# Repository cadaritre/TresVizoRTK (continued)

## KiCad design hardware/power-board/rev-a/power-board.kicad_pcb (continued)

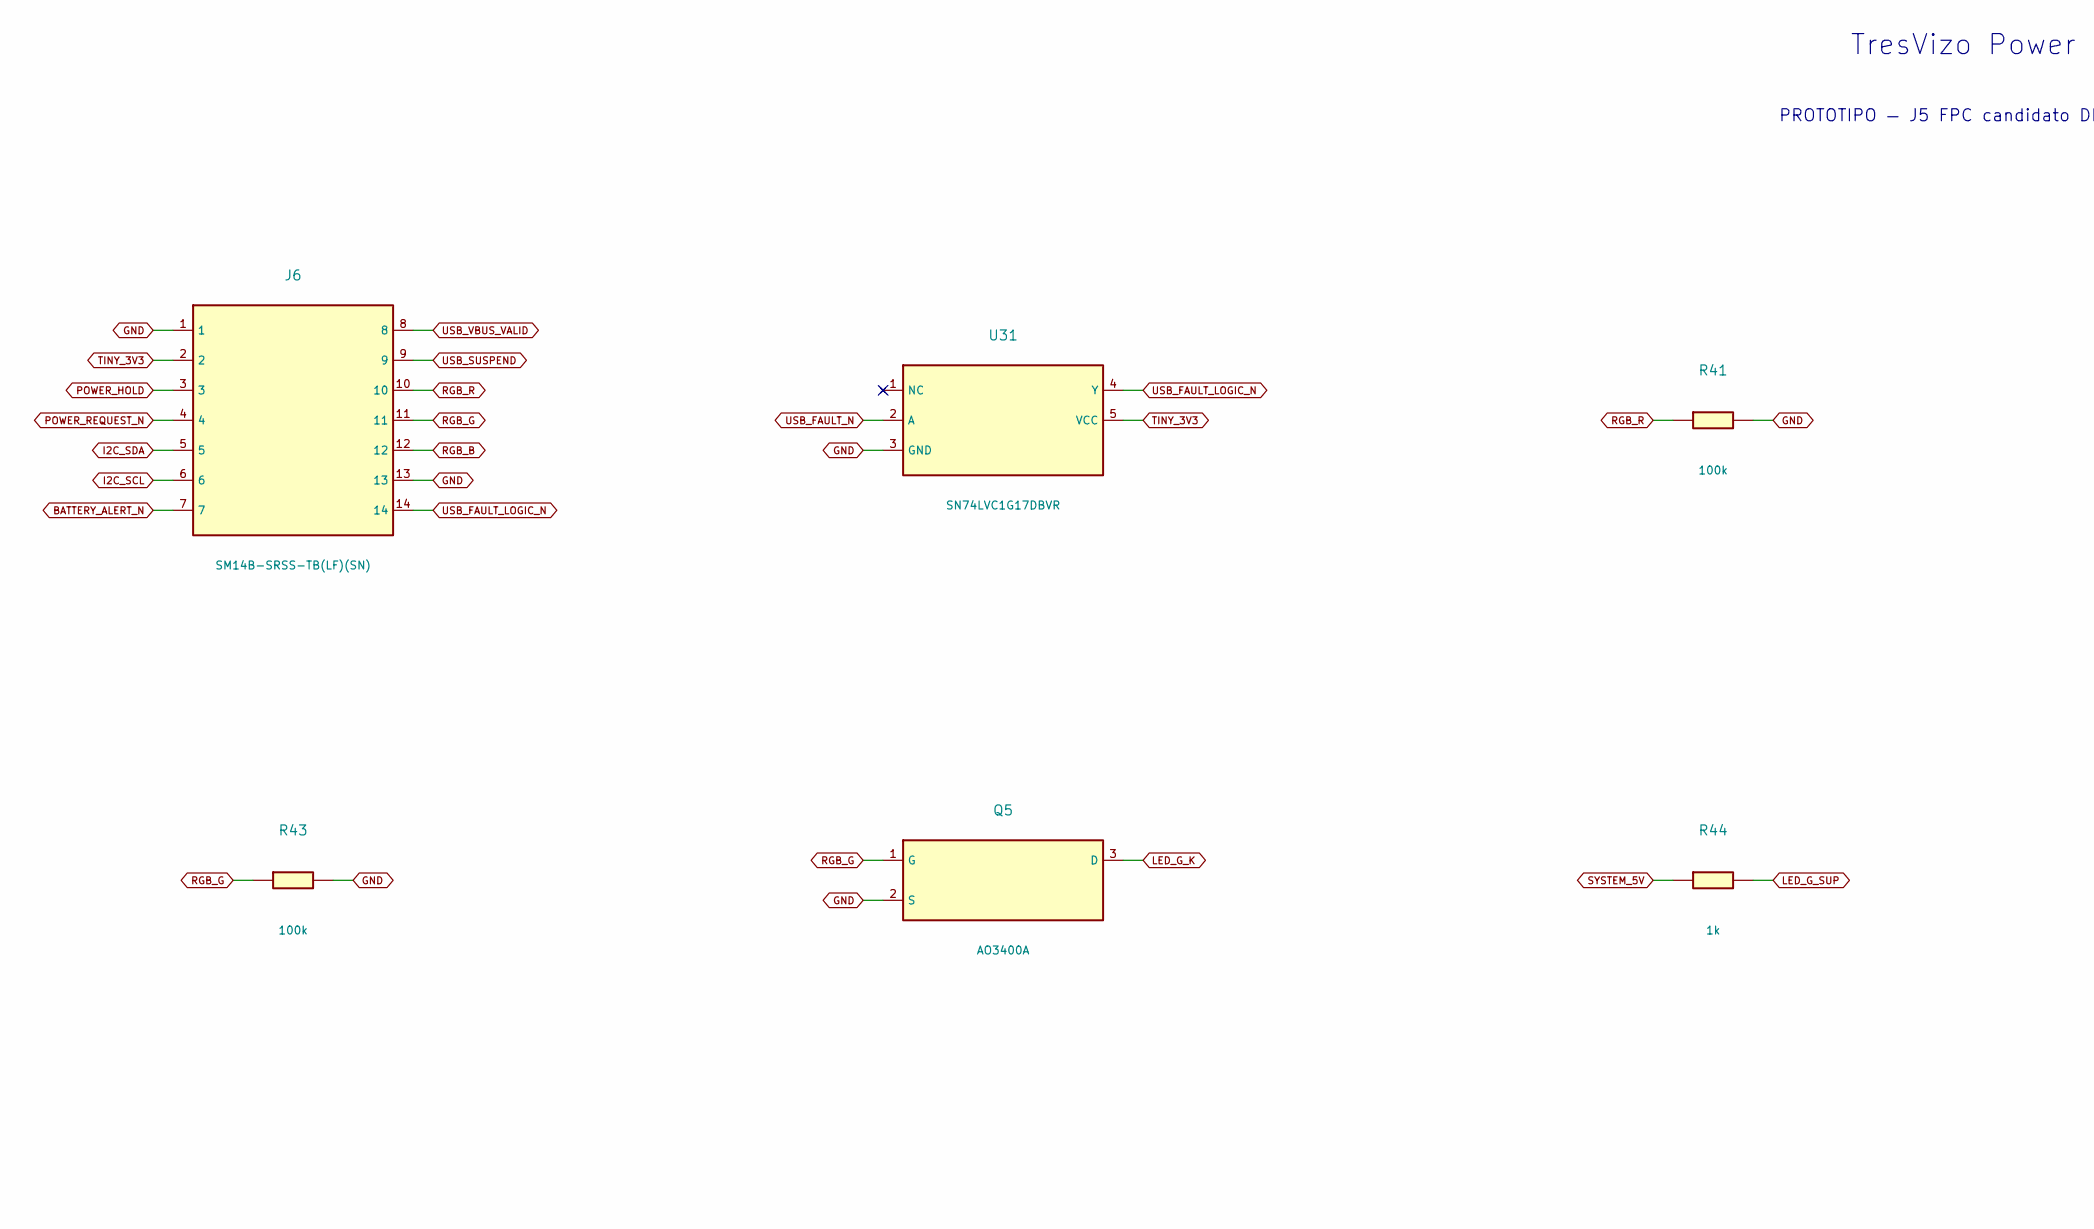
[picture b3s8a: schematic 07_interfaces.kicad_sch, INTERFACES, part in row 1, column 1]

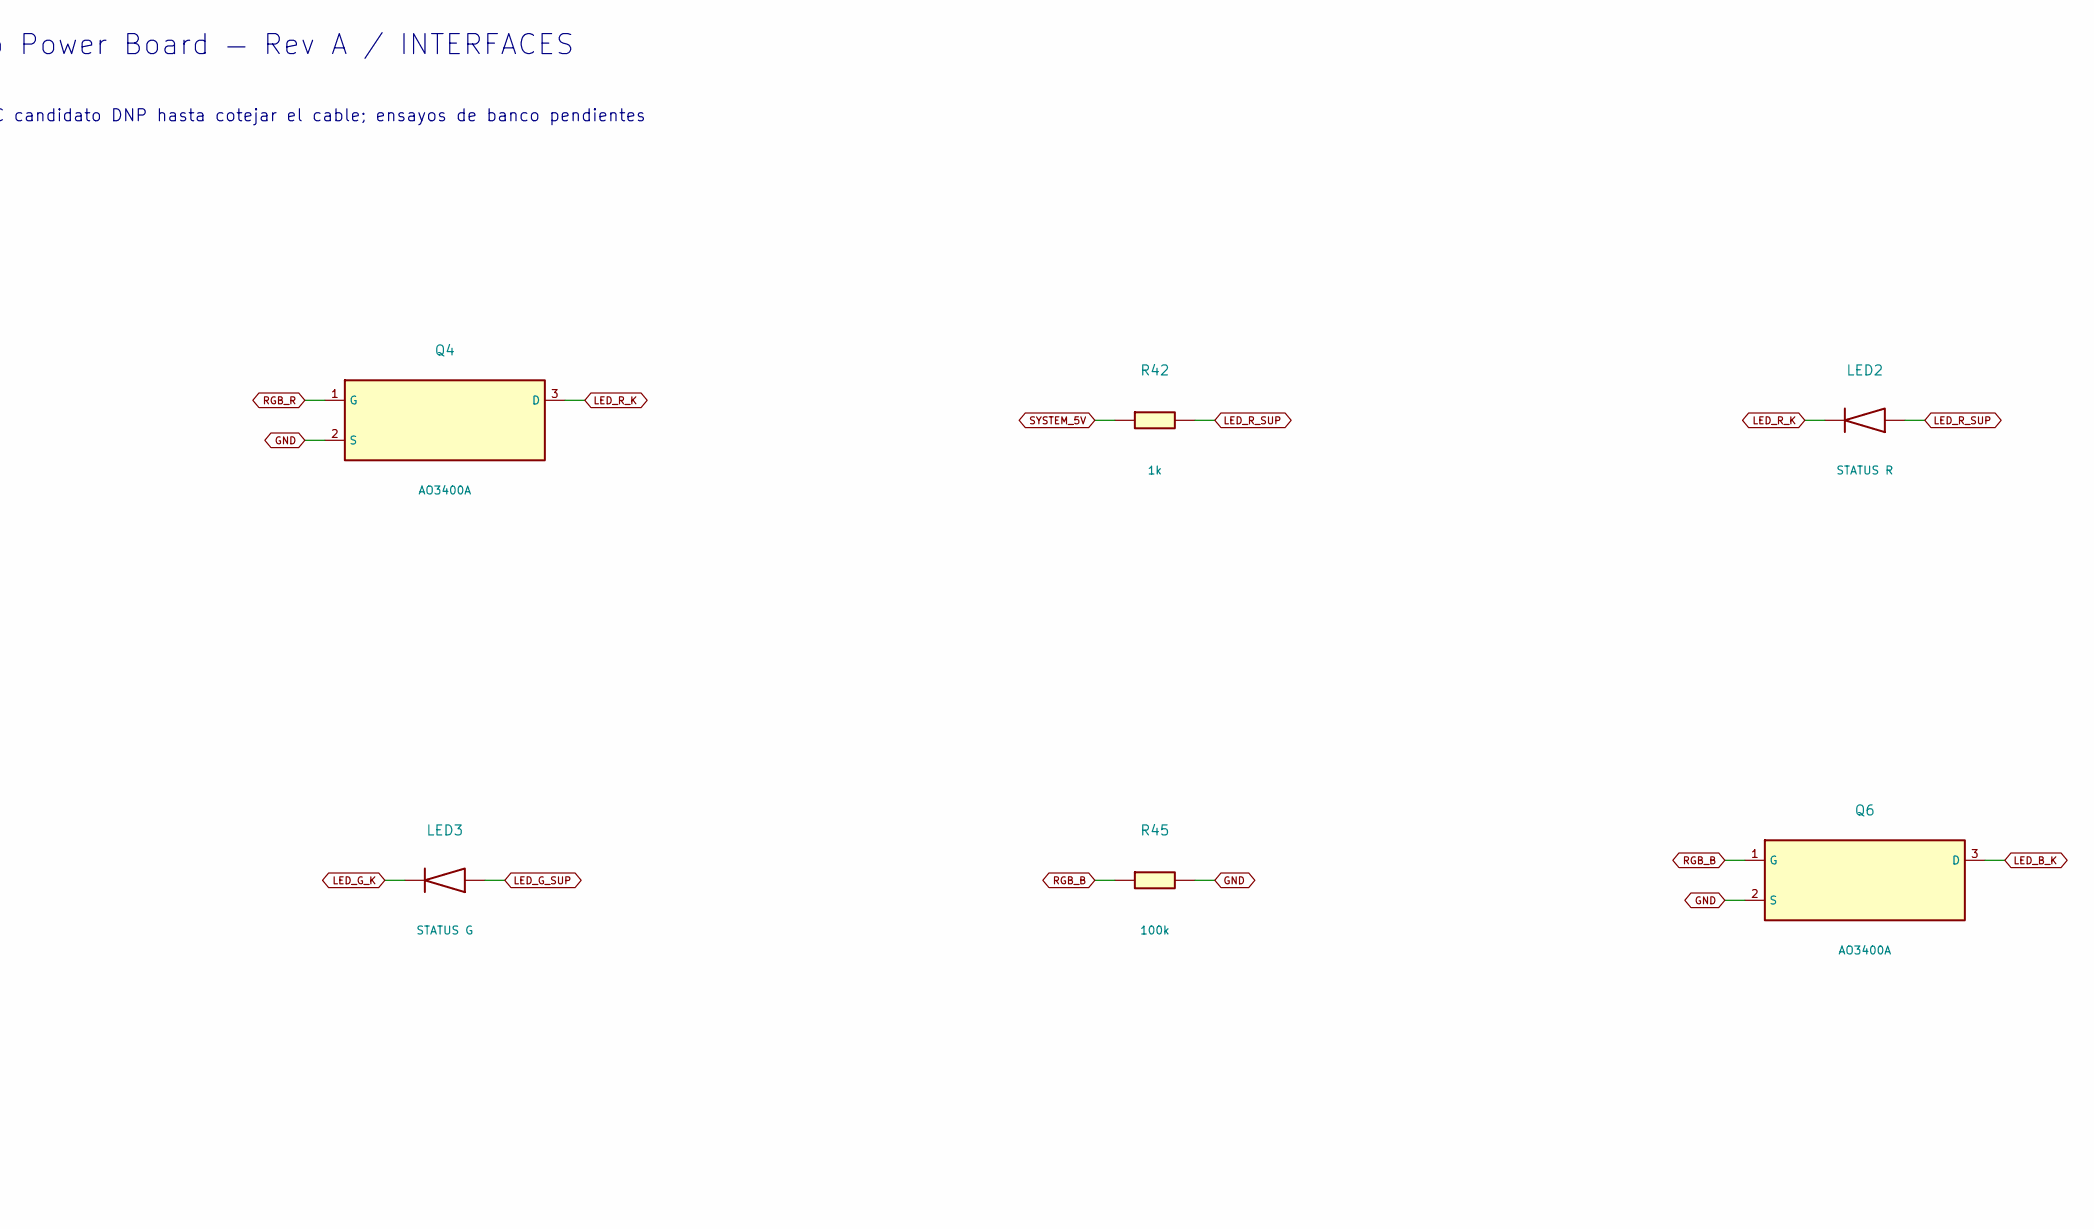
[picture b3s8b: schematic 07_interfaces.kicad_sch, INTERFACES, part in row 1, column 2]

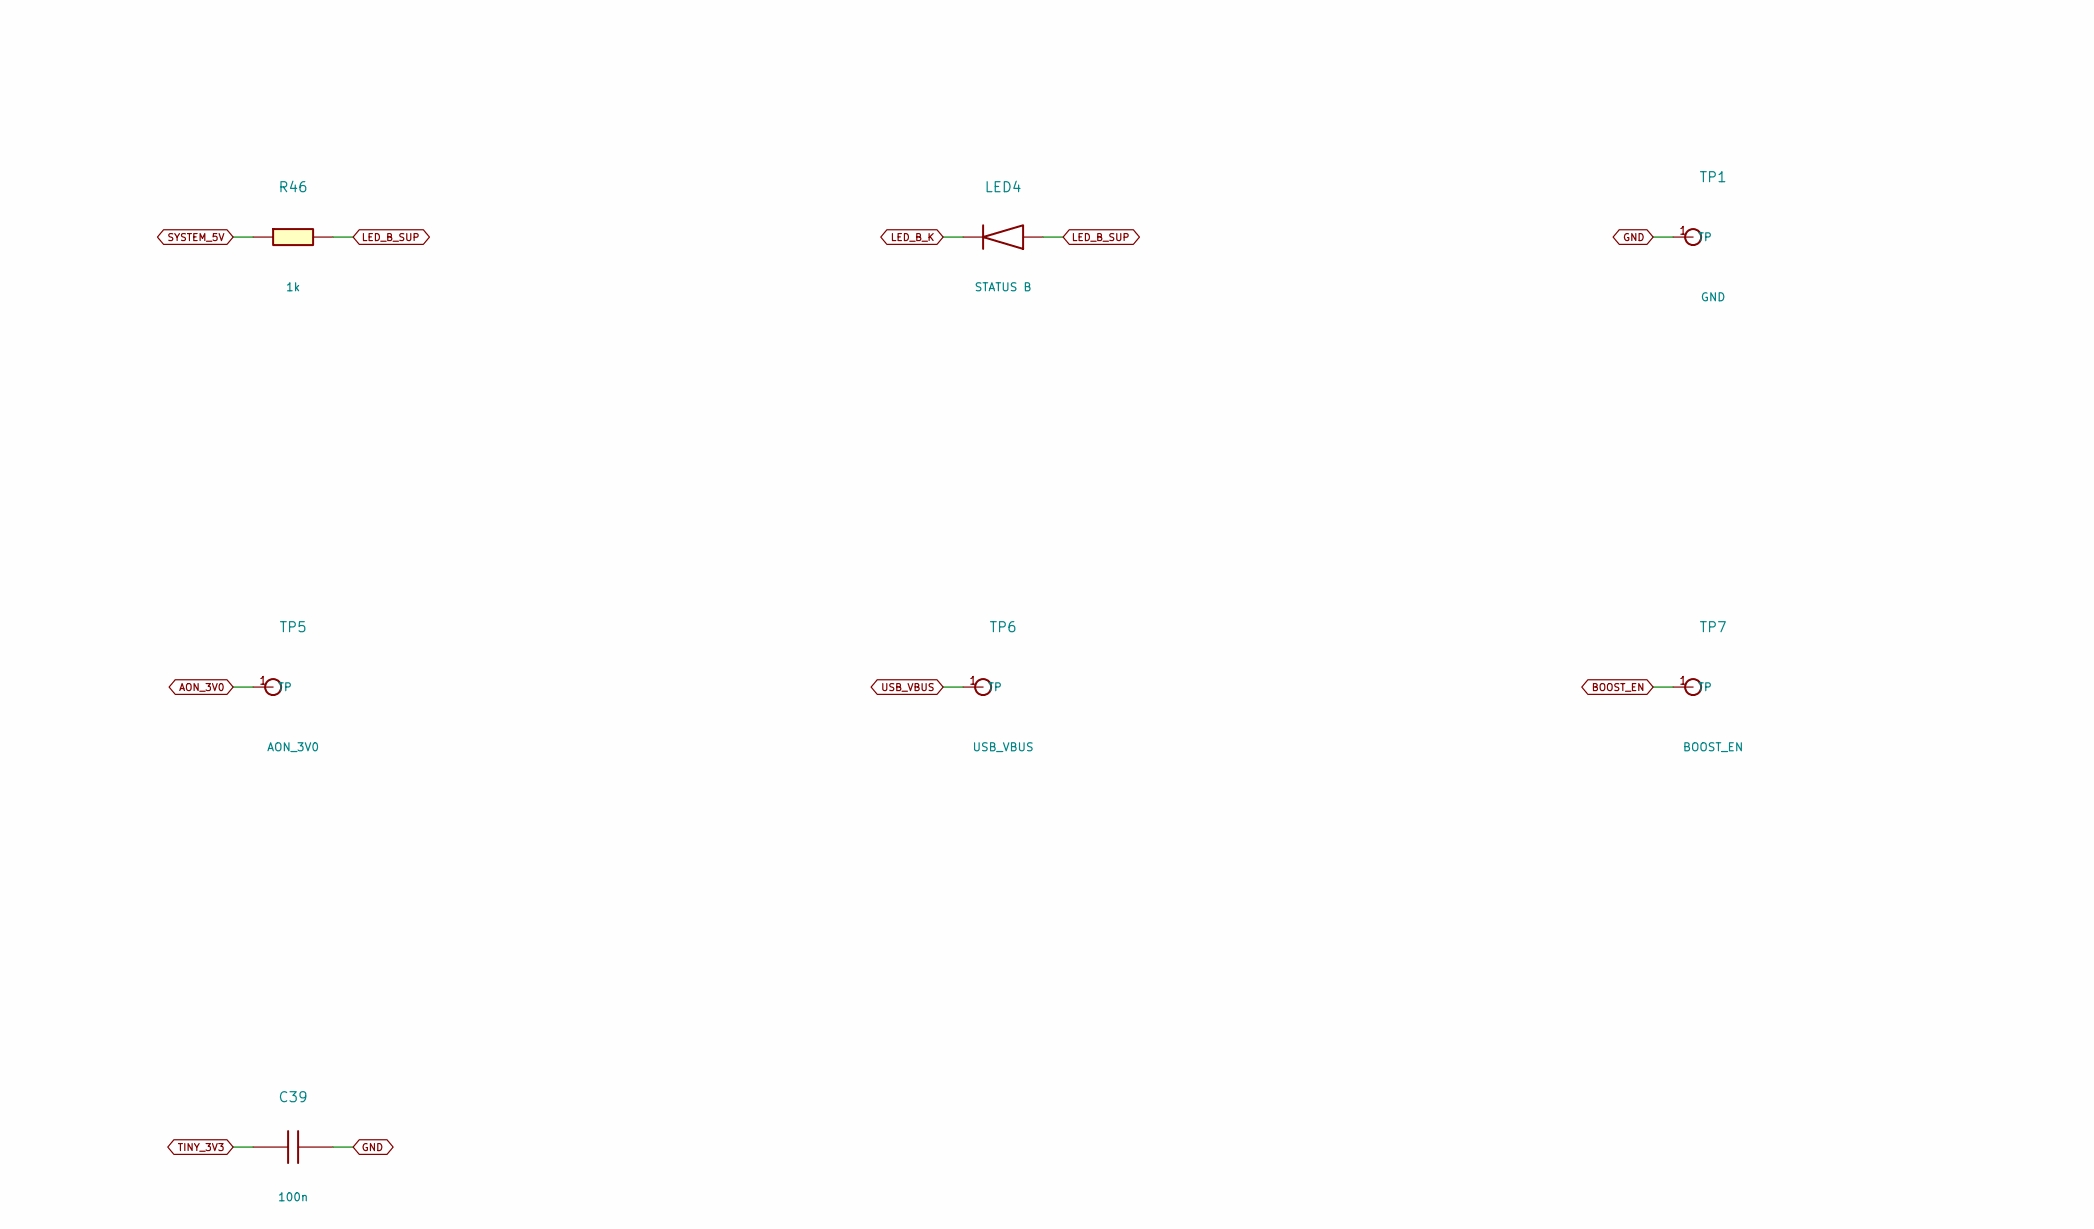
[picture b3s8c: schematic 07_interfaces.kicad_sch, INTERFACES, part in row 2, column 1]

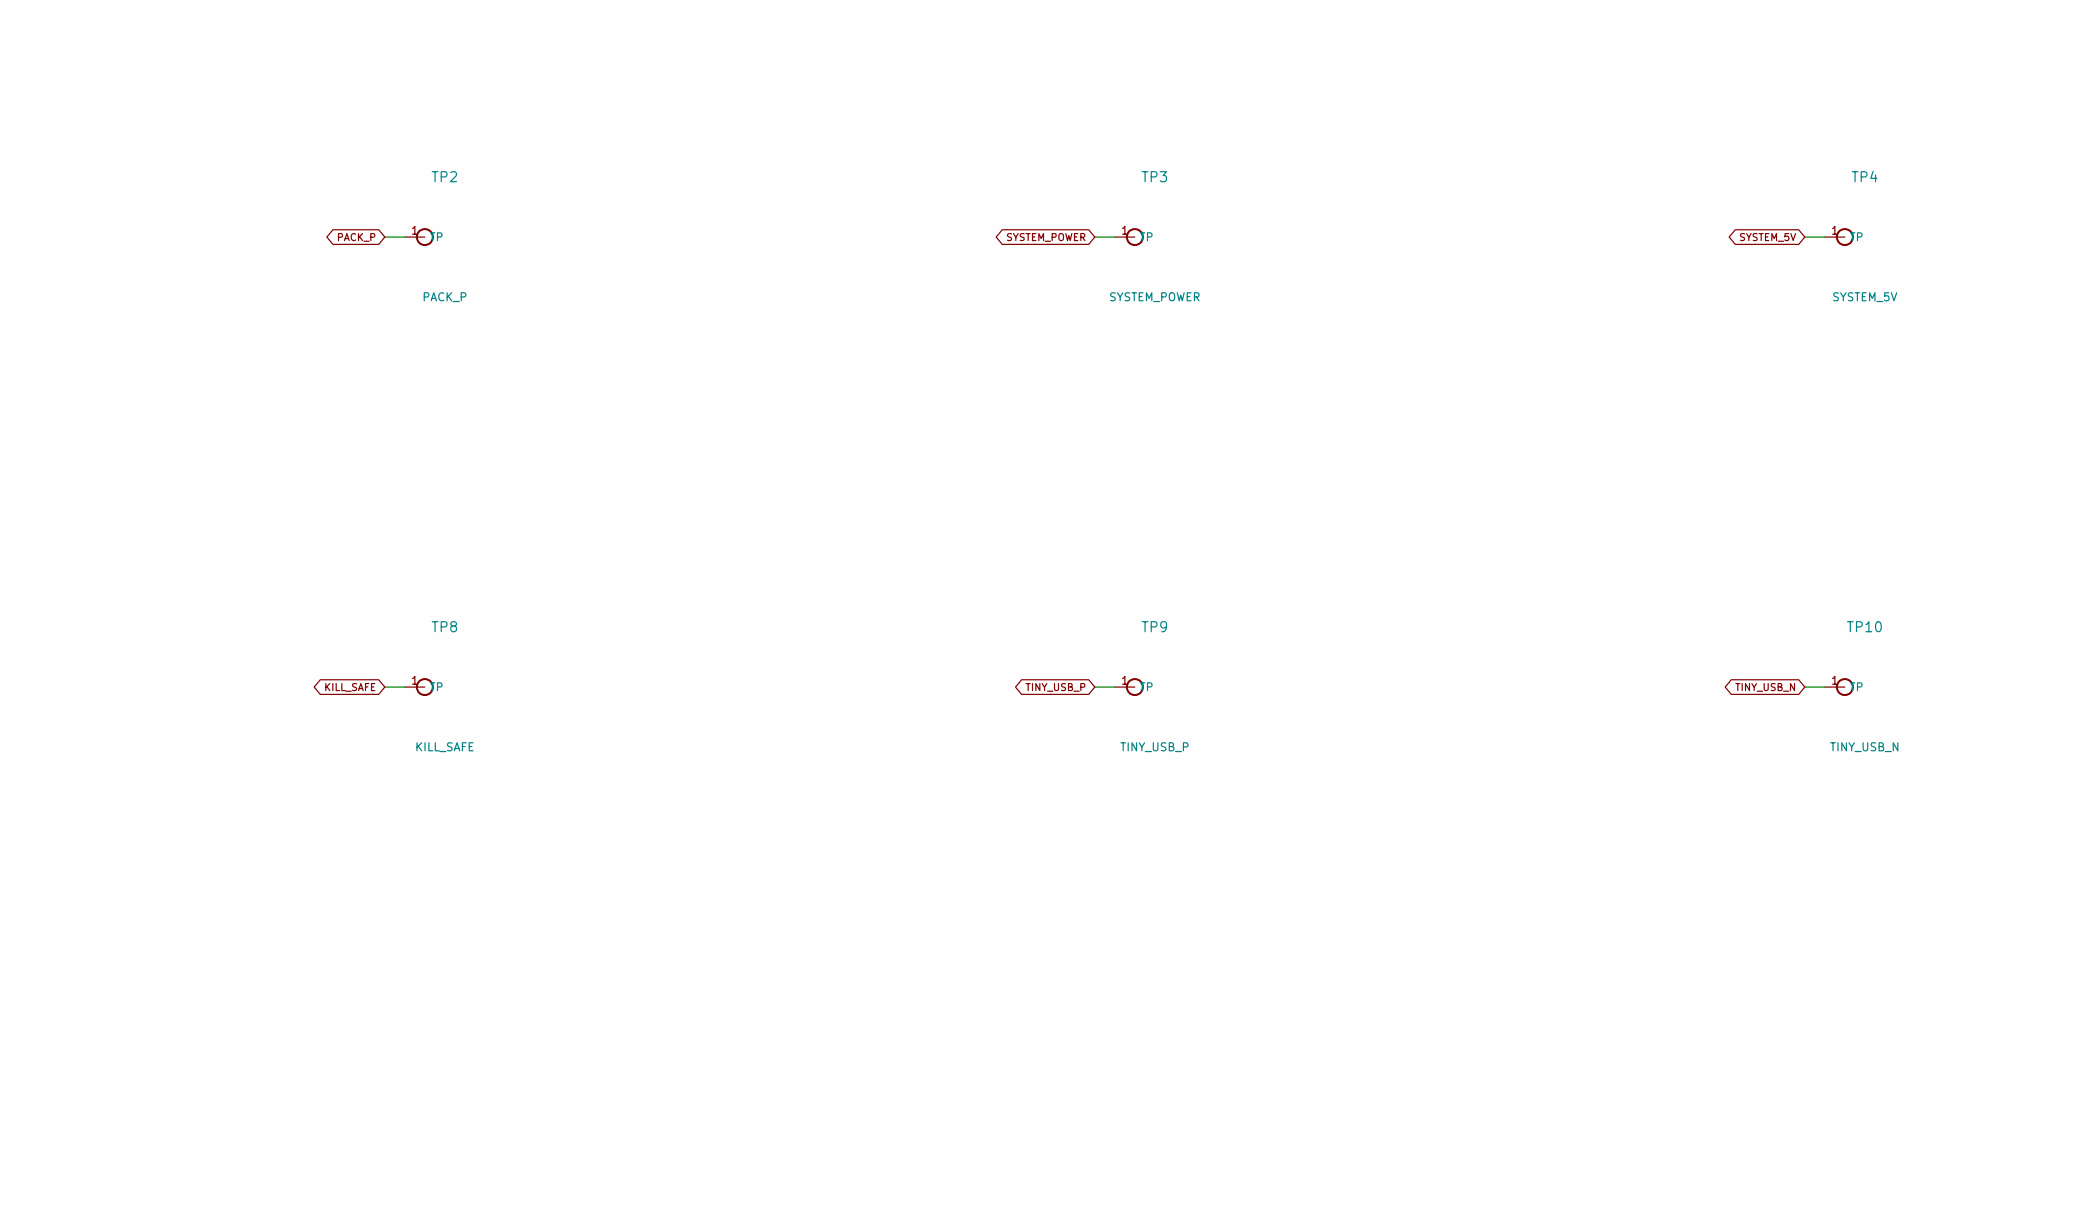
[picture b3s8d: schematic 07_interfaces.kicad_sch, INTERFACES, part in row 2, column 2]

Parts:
C39: 100n; C_0603_1608Metric; MPN CC0603KRX7R9BB104
J6: SM14B-SRSS-TB(LF)(SN); JST_SH_SM14B-SRSS-TB_1x14-1MP_P1.00mm_Horizontal; MPN SM14B-SRSS-TB(LF)(SN)
LED2: STATUS R; LED_0603_1608Metric; MPN LTST-C190KRKT
LED3: STATUS G; LED_0603_1608Metric; MPN LTST-C190KGKT
LED4: STATUS B; LED_0603_1608Metric; MPN LTST-C190TBKT
Q4, Q5, Q6: AO3400A; SOT-23; MPN AO3400A
R41, R43, R45: 100k; R_0603_1608Metric; MPN RC0603FR-07100KL
R42, R44, R46: 1k; R_0603_1608Metric; MPN RC0603FR-071KL
TP1: GND; TestPoint_Pad_D1.0mm; MPN TestPoint
TP2: PACK_P; TestPoint_Pad_D1.0mm; MPN TestPoint
TP3: SYSTEM_POWER; TestPoint_Pad_D1.0mm; MPN TestPoint
TP4: SYSTEM_5V; TestPoint_Pad_D1.0mm; MPN TestPoint
TP5: AON_3V0; TestPoint_Pad_D1.0mm; MPN TestPoint
TP6: USB_VBUS; TestPoint_Pad_D1.0mm; MPN TestPoint
TP7: BOOST_EN; TestPoint_Pad_D1.0mm; MPN TestPoint
TP8: KILL_SAFE; TestPoint_Pad_D1.0mm; MPN TestPoint
TP9: TINY_USB_P; TestPoint_Pad_D1.0mm; MPN TestPoint
TP10: TINY_USB_N; TestPoint_Pad_D1.0mm; MPN TestPoint
U31: SN74LVC1G17DBVR; SOT-23-5; MPN SN74LVC1G17DBVR

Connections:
AON_3V0: TP5.1; also elsewhere on the board
BATTERY_ALERT_N: J6.7; also elsewhere on the board
BOOST_EN: TP7.1; also elsewhere on the board
GND: C39.2, J6.1, J6.13, Q4.2 (S), Q5.2 (S), Q6.2 (S), R41.2, R43.2, R45.2, TP1.1, U31.3 (GND); also elsewhere on the board
I2C_SCL: J6.6; also elsewhere on the board
I2C_SDA: J6.5; also elsewhere on the board
KILL_SAFE: TP8.1; also elsewhere on the board
LED_B_K: LED4.1 (K), Q6.3 (D)
LED_B_SUP: LED4.2 (A), R46.2
LED_G_K: LED3.1 (K), Q5.3 (D)
LED_G_SUP: LED3.2 (A), R44.2
LED_R_K: LED2.1 (K), Q4.3 (D)
LED_R_SUP: LED2.2 (A), R42.2
PACK_P: TP2.1; also elsewhere on the board
POWER_HOLD: J6.3; also elsewhere on the board
POWER_REQUEST_N: J6.4; also elsewhere on the board
RGB_B: J6.12, Q6.1 (G), R45.1
RGB_G: J6.11, Q5.1 (G), R43.1
RGB_R: J6.10, Q4.1 (G), R41.1
SYSTEM_5V: R42.1, R44.1, R46.1, TP4.1; also elsewhere on the board
SYSTEM_POWER: TP3.1; also elsewhere on the board
TINY_3V3: C39.1, J6.2, U31.5 (VCC); also elsewhere on the board
TINY_USB_N: TP10.1; also elsewhere on the board
TINY_USB_P: TP9.1; also elsewhere on the board
USB_FAULT_LOGIC_N: J6.14, U31.4 (Y)
USB_FAULT_N: U31.2 (A); also elsewhere on the board
USB_SUSPEND: J6.9; also elsewhere on the board
USB_VBUS: TP6.1; also elsewhere on the board
USB_VBUS_VALID: J6.8; also elsewhere on the board

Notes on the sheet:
TresVizo Power Board — Rev A / INTERFACES
PROTOTIPO — J5 FPC candidato DNP hasta cotejar el cable; ensayos de banco pendientes

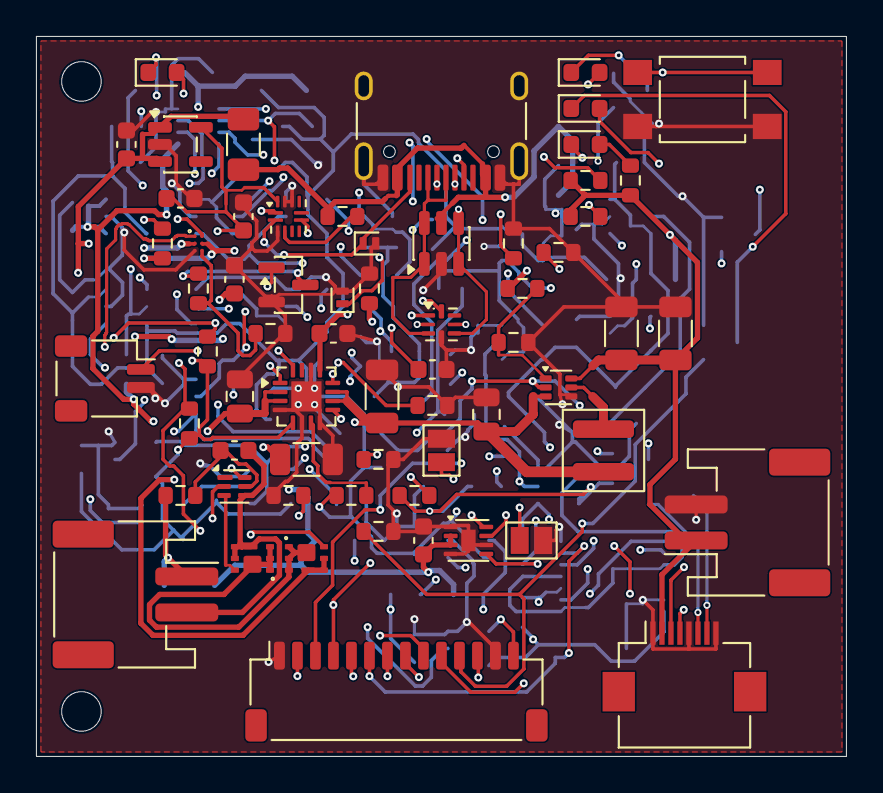
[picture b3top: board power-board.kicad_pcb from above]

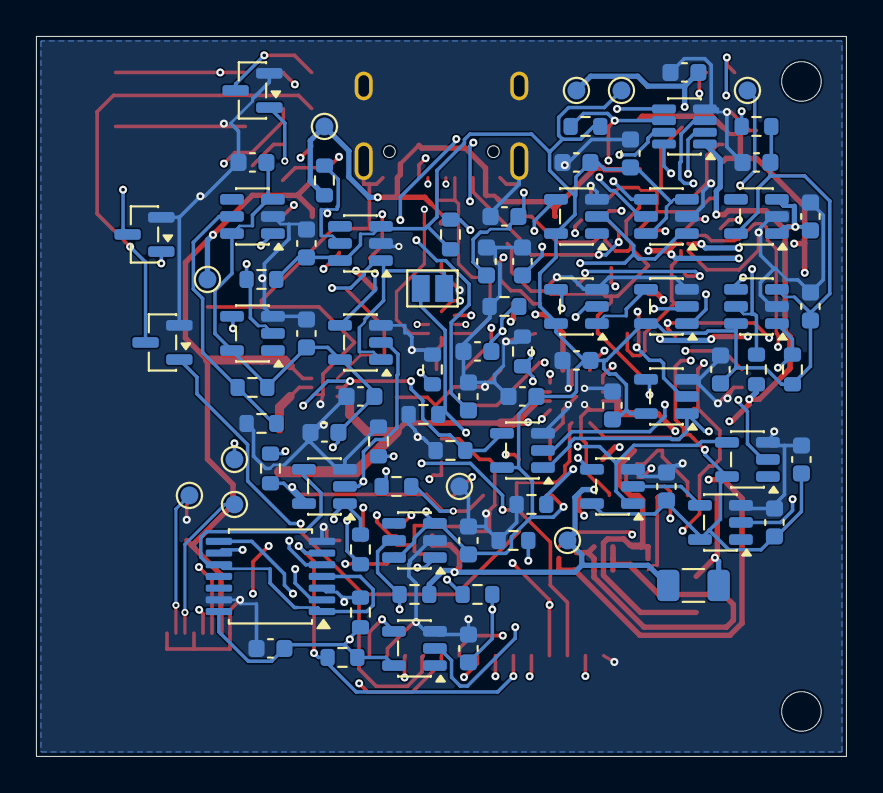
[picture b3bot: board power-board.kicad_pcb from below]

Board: 4 copper layers, 45.0 x 40.0 mm, 151 parts (85 on the bottom side), 85 nets.

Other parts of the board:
H1, H2: M2 NPTH

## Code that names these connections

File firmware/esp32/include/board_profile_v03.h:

#pragma once

// MeridianV, placa principal v0.3 compacta (hardware/main-board, pedido a JLCPCB
// en el commit 97000ef). ESP32-S3-WROOM-1-N16R2 soldado: 16 MB de flash quad y
// 2 MB de PSRAM quad, así que GPIO33-37 quedan libres (los usaría una PSRAM octal).
//
// **Fuente de verdad: el netlist de esa placa** (hardware/main-board/kicad/
// tresvizo-main.net, idéntico al que exporta kicad-cli del esquema de 97000ef).
// Cada pin lleva su red y el pin del módulo U201. `tools/board_check/
// check_v03_pins.py` compara este archivo con el netlist y falla si algo no
// coincide: si la placa cambia, se cambia aquí y se vuelve a correr.
// Hojas: Espressif ESP32-S3-WROOM-1 v1.8 (tabla 3-1, pines del módulo), TI
// BQ25798 SLUSDV2C (rev. C, junio 2026), Bosch BST-BMI088-DS001 rev 1.9.
#define TRESVIZO_HARDWARE_ID "tresvizo-meridianv-v03-s3-16m-v1"
// UART del UM980: COM2 de la carrier BDLX a 115200 (J301.3/4).
#define TRESVIZO_GNSS_RX 9    // U201.17, GNSS_TXD2_MCU, R305 100 Ω ← TXD2 (J301.4)
#define TRESVIZO_GNSS_TX 8    // U201.12, GNSS_TX_MCU, R304 1 kΩ → RXD2 (J301.3)
#define TRESVIZO_GNSS_BAUD 115200

namespace board_profile {
constexpr char kHardwareId[] = TRESVIZO_HARDWARE_ID;
constexpr char kName[] = "TresVizo MeridianV v0.3 (ESP32-S3-WROOM-1-N16R2)";

// I2C de la OLED (J403), el cargador BQ25798 (U102) y el medidor MAX17048 (U103).
// Pull-ups de 4.7 kΩ en placa (R204, R205).
constexpr int kSda = 13;   // U201.21, I2C_SDA
constexpr int kScl = 14;   // U201.22, I2C_SCL
constexpr unsigned char kChargerAddress = 0x6B;  // BQ25798, SLUSDV2C §7.3.14.5
constexpr unsigned char kGaugeAddress = 0x36;    // MAX17048
// La OLED va a +3V3 directo: no hay regulador de periféricos que encender.
constexpr int kPeripheralEnable = -1;
// El módulo va girado 180° en su plano (research/v03-compacta.md, «Valores para
// el firmware»): se gira la imagen, no se espeja. Cuartos de vuelta de Adafruit GFX.
constexpr int kOledRotation = 2;

// microSD TF-015 (J401), SD_MMC de 4 bits. CMD y D0-D3 con 10 kΩ a +3V3 (R401-R405).
constexpr int kSdClock = 6;     // U201.6, SD_CLK (sin resistencia en serie)
constexpr int kSdCommand = 7;   // U201.7, SD_CMD
constexpr int kSdD0 = 5;        // U201.5, SD_D0
constexpr int kSdD1 = 4;        // U201.4, SD_D1
constexpr int kSdD2 = 16;       // U201.9, SD_D2
constexpr int kSdD3 = 15;       // U201.8, SD_D3
// Detección: el contacto CD del TF-015 cierra a GND con tarjeta (SD_CD_N, 10 kΩ a
// +3V3 por R406); Q401 (AO3401A, canal P) lo invierte: SD_DET en HIGH con tarjeta,
// R407 de 100 kΩ a GND sin ella. No hace falta pull interno.
constexpr int kSdDetect = 17;   // U201.10, SD_DET
constexpr bool kSdDetectActiveLow = false;
constexpr bool kSdDetectInternalPull = false;

// Botón SW401 a BTN_N: despierta al cargador (QON) y llega a GPIO18 por D402
// (1N4148W, ánodo en el GPIO). Activo bajo, R408 de 10 kΩ a +3V3. Mantenerlo
// 10 s es el reset por hardware del BQ25798 (SLUSDV2C §7.3.12.3).
constexpr int kPowerButton = 18;   // U201.11, BTN_SENSE_N
constexpr int kPowerPush = kPowerButton;
// Sin GPIO de corte: el apagado es el modo «ship» del BQ25798 por I2C (Q101).
constexpr int kPowerOff = -1;
// LED rojo D403 por R409 (330 Ω): activo alto, ~4.4 mA. Sin pull en el reset.
constexpr int kStatusLed = 48;     // U201.25, LED_STATUS
// INT del cargador y ALRT del medidor, drenador abierto con 10 kΩ (R108, R113).
constexpr int kChargerInt = 21;    // U201.23, CHG_INT_N
constexpr int kGaugeAlert = 47;    // U201.24, FG_ALRT_N

// GNSS: carrier BDLX por J301 y su 5 V del TPS63070 (U301).
// GPIO45 es pin de arranque (VDD_SPI) con R301 de 100 kΩ a GND: en el reset el
// GNSS queda apagado y el firmware lo enciende. Cualquier reinicio del ESP32 lo
// apaga y el UM980 arranca de cero.
constexpr int kGnssPowerEnable = 45;  // U201.26, GNSS_PWR_EN → EN del TPS63070
constexpr int kGnssPps = 10;          // U201.18, GNSS_PPS_MCU, R306 100 Ω ← J301.5
constexpr int kGnssEvent = 11;        // U201.19, GNSS_EVENT_MCU, R307 1 kΩ → J301.6, R308 100 kΩ a GND
// RESET_N: drenador abierto, pulso ≥ 5 ms. La BDLX no lo saca: el firmware no lo maneja.
constexpr int kGnssReset = 12;        // U201.20, GNSS_RESET_MCU, R309 1 kΩ → J301.7

// BMI088 (U401) en un segundo bus I2C (Wire1), 400 kHz, pull-ups de 4.7 kΩ
// (R411, R412). PS y CSB1 a VDDIO (I2C), CSB2 al aire, SDO1/SDO2 a GND.
constexpr int kImuSda = 41;    // U201.34, IMU_SDA
constexpr int kImuScl = 42;    // U201.35, IMU_SCL
constexpr int kImuInt1 = 2;    // U201.38, IMU_INT1 ← INT1 del acelerómetro (U401.16), sin pull-up
constexpr int kImuInt3 = 1;    // U201.39, IMU_INT3 ← INT3 del giróscopo (U401.12), sin pull-up
constexpr unsigned char kImuAccelAddress = 0x18;  // SDO1 a GND (DS §6.2)
constexpr unsigned char kImuGyroAddress = 0x68;   // SDO2 a GND (DS §6.2)

// USB nativo (USB-C J101, por U101) y consola UART0 en puntos de prueba.
constexpr int kUsbDm = 19, kUsbDp = 20;          // U201.13 / U201.14
constexpr int kConsoleTx = 43, kConsoleRx = 44;  // TP208 / TP209

// Batería: pack comercial 1S2P (2 × 18650 Li-ion en paralelo, BMS 4.30/2.80 V).
constexpr int kBatteryCapacityMah = 5600;   // según el anuncio; sin medir
// En «ship» el BQ2579x necesita la celda por encima de ~3.4 V: se apaga antes.
constexpr float kLowBatteryVolts = 3.5f;
constexpr float kAutoShutdownVolts = 3.45f;
constexpr unsigned long kAutoShutdownHoldMs = 60000;
// Cargador: química y límites del pack (README de la placa, «Valores de seguridad»).
constexpr unsigned kChargeVoltageMv = 4200;   // VREG de 1S que fija PROG (R103 4.7 kΩ)
constexpr unsigned kChargeCurrentMa = 1000;   // ICHG que escribe el firmware
constexpr unsigned kChargeCurrentMaxMa = 1500; // dos contactos GH por polo, AWG #26
static_assert(kChargeCurrentMa <= kChargeCurrentMaxMa, "ICHG por encima del límite del conector J102");

// Identidad del producto (docs/api-contract/receiver-identity.md): es un
// MeridianV y sigue anunciando «MeridianV» por BLE, Wi-Fi y mDNS.
constexpr char kModel[] = "MeridianV";
constexpr unsigned char kModelCode = 5;
constexpr bool kPerUnitNetworkName = false;
constexpr char kGnssModule[] = "UM980";
constexpr bool kLoraIntegrated = false;
constexpr const char* kImu = "BMI088";           // en la placa (U401); sin driver todavía
constexpr char kBatteryChemistry[] = "li-ion";
constexpr bool kRemovableStorage = true;         // microSD de empuje, accesible por el costado
constexpr const char* kIpRating = nullptr;
}

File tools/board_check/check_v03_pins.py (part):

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            report.check(gpio == 45 and constant == 'kGnssPowerEnable' and netlist.resistor_to(net, 'GND'),
                         f'{constant}: GPIO{gpio} es pin de arranque y no tiene el pull-down que lo deja bajo en el reset.')
    report.check('N16R2' in v.get('U201', ''), 'U201: PSRAM octal (R8) ocuparía GPIO33-37.')
    report.check(netlist.resistor_to('ESP_IO3', 'GND') != [], 'GPIO3 (pin de arranque JTAG) sin su resistencia a GND.')
    report.check(netlist.resistor_to('ESP_BOOT', '+3V3') != [], 'GPIO0 (BOOT) sin pull-up: no arrancaría desde la flash.')

    # UART, PPS, EVENT y RESET del GNSS hasta J301 (resistencias en serie).
    for net, ref, j301_pin in (('GNSS_TX_MCU', 'R304', '3'), ('GNSS_TXD2_MCU', 'R305', '4'), ('GNSS_PPS_MCU', 'R306', '5'),
                               ('GNSS_EVENT_MCU', 'R307', '6'), ('GNSS_RESET_MCU', 'R309', '7')):
        far = netlist.other_side(ref, net)
        report.check(far is not None and far == netlist.net_of('J301', j301_pin),
                     f'{net}: no llega a J301.{j301_pin} por {ref}.')
    report.check(netlist.resistor_to('GNSS_EVENT_MCU', 'GND') != [], 'EVENT sin pull-down (R308).')
    report.check(pin_to(netlist, 'U301', 'EN') == 'GNSS_PWR_EN', 'GNSS_PWR_EN no llega al EN del TPS63070.')
    report.check(netlist.resistor_to('GNSS_PWR_EN', 'GND') != [], 'GNSS_PWR_EN sin pull-down: el GNSS no quedaría apagado en el reset.')

    # I2C principal: OLED, cargador y medidor; direcciones fijas de esos chips.
    for net, oled_pin in (('I2C_SDA', '4'), ('I2C_SCL', '3')):
        report.check(netlist.resistor_to(net, '+3V3') != [], f'{net} sin pull-up.')
        report.check(netlist.net_of('J403', oled_pin) == net, f'{net}: no llega a la OLED (J403.{oled_pin}).')
    report.check(pin_to(netlist, 'U102', 'SDA') == 'I2C_SDA' and pin_to(netlist, 'U102', 'SCL') == 'I2C_SCL',
                 'El BQ25798 no está en el I2C principal.')
    report.check(pin_to(netlist, 'U103', 'SDA') == 'I2C_SDA' and pin_to(netlist, 'U103', 'SCL') == 'I2C_SCL',
                 'El MAX17048 no está en el I2C principal.')
    report.check(profile.get('kChargerAddress') == 0x6B, 'kChargerAddress: el BQ25798 es 0x6B (SLUSDV2C §7.3.14.5).')
    report.check(profile.get('kGaugeAddress') == 0x36, 'kGaugeAddress: el MAX17048 es 0x36.')
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    # Botón: activo bajo por D402 desde QON; LED activo alto.
    report.check(netlist.resistor_to('BTN_SENSE_N', '+3V3') != [], 'BTN_SENSE_N sin pull-up.')
    anode, cathode = netlist.net_of('D402', '2'), netlist.net_of('D402', '1')
    report.check(anode == 'BTN_SENSE_N' and cathode == 'BTN_N', 'D402: ánodo en GPIO18 y cátodo en BTN_N.')
    report.check(pin_to(netlist, 'U102', 'QON') == 'BTN_N', 'El botón no llega a QON del BQ25798.')
    report.check(netlist.net_of('SW401', '4') == 'GND' or netlist.net_of('SW401', '1') == 'GND',
                 'SW401 no cierra a GND: el botón no sería activo bajo.')
    led_resistor = [n.ref for n in netlist.nodes('LED_STATUS') if n.ref.startswith('R')]
    led_anode = netlist.other_side(led_resistor[0], 'LED_STATUS') if led_resistor else None
    report.check(led_anode is not None and netlist.net_of('D403', '2') == led_anode and netlist.net_of('D403', '1') == 'GND',
                 'LED_STATUS: se esperaba GPIO → resistencia → ánodo de D403, cátodo a GND (activo alto).')

    # Cargador: PROG (1S), FET de envío y /CE.
    prog = netlist.pin_by_function('U102', 'PROG')
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    report.check(pin_to(netlist, 'U102', 'CE') == 'GND', '/CE del BQ25798 no está a GND.')
    report.check(isinstance(profile.get('kChargeCurrentMa'), int) and profile.get('kChargeCurrentMa') <= 1500
                 and profile.get('kChargeCurrentMaxMa') == 1500, 'ICHG: 1.5 A como mucho (J102, AWG #26).')
    report.check(pin_to(netlist, 'U102', 'INT') == 'CHG_INT_N' and netlist.resistor_to('CHG_INT_N', '+3V3') != [],
                 'INT del BQ25798 sin su pull-up.')
    report.check(pin_to(netlist, 'U103', 'ALRT') == 'FG_ALRT_N' and netlist.resistor_to('FG_ALRT_N', '+3V3') != [],
                 'ALRT del MAX17048 sin su pull-up.')

    # BMI088: I2C (PS y CSB1 a VDDIO), direcciones por SDO1/SDO2, interrupciones.
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                 f'Dirección del acelerómetro: SDO1 en {sdo1} → {"0x18" if sdo1 == "GND" else "0x19"} (DS §6.2).')
    report.check(profile.get('kImuGyroAddress') == (0x68 if sdo2 == 'GND' else 0x69),
                 f'Dirección del giróscopo: SDO2 en {sdo2} → {"0x68" if sdo2 == "GND" else "0x69"} (DS §6.2).')
    report.check(pin_to(netlist, 'U401', 'SDI/SDA') == 'IMU_SDA' and pin_to(netlist, 'U401', 'SCK/SCL') == 'IMU_SCL',
                 'El BMI088 no está en IMU_SDA/IMU_SCL.')
    report.check(pin_to(netlist, 'U401', 'INT1') == 'IMU_INT1' and pin_to(netlist, 'U401', 'INT3') == 'IMU_INT3',
                 'INT1/INT3 del BMI088 no llegan a IMU_INT1/IMU_INT3.')
    for net in ('IMU_SDA', 'IMU_SCL'):
        report.check(netlist.resistor_to(net, '+3V3') != [], f'{net} sin pull-up.')
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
